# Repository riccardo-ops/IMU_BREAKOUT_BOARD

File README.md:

In this repo, a simple breakout board is made to include an IMU and a barometer.

IMU = LSM6DSV16XTR -> https://www.mouser.it/it/ProductDetail/STMicroelectronics/LSM6DSV16XTR?qs=MyNHzdoqoQLCWe%2FE3pkKcA%3D%3D
Barometer = MS5611-01BA03 -> https://www.te.com/commerce/DocumentDelivery/DDEController?Action=showdoc&DocId=Data+Sheet%7FMS5611-01BA03%7FB3%7Fpdf%7FEnglish%7FENG_DS_MS5611-01BA03_B3.pdf%7FCAT-BLPS0036

The idea is simple : create a breakout board with two common and low cost sensors that can easily be interfaced with FPGAs, Arduino, STM32, etc.

Some tips for this board : 
- Connectors : simple pin header, every Arduino starter pack has compatible cables.
- User LED : two user controlled LED are put inside this board
- Power on LED : there's an LED connected to the power section of every IC. 
  If something goes wrong with power connections, the LED is a simple, but yet effective way to debug
- TVS Diode : those connectors can easily have transient current peaks. Burn the ICs in not something I want, so this kind of protection is needed.
  Every TVS diode eats some voltage, so keep this in mind when you design your protection module!
- 4 Layer : this can be overkill, but to have a solid ground plane is always a good idea when you use sensible sensors like IMU and barometers.
  In this project the maximum frequency of communication is 5 MHz, so there is no danger for high frequency.

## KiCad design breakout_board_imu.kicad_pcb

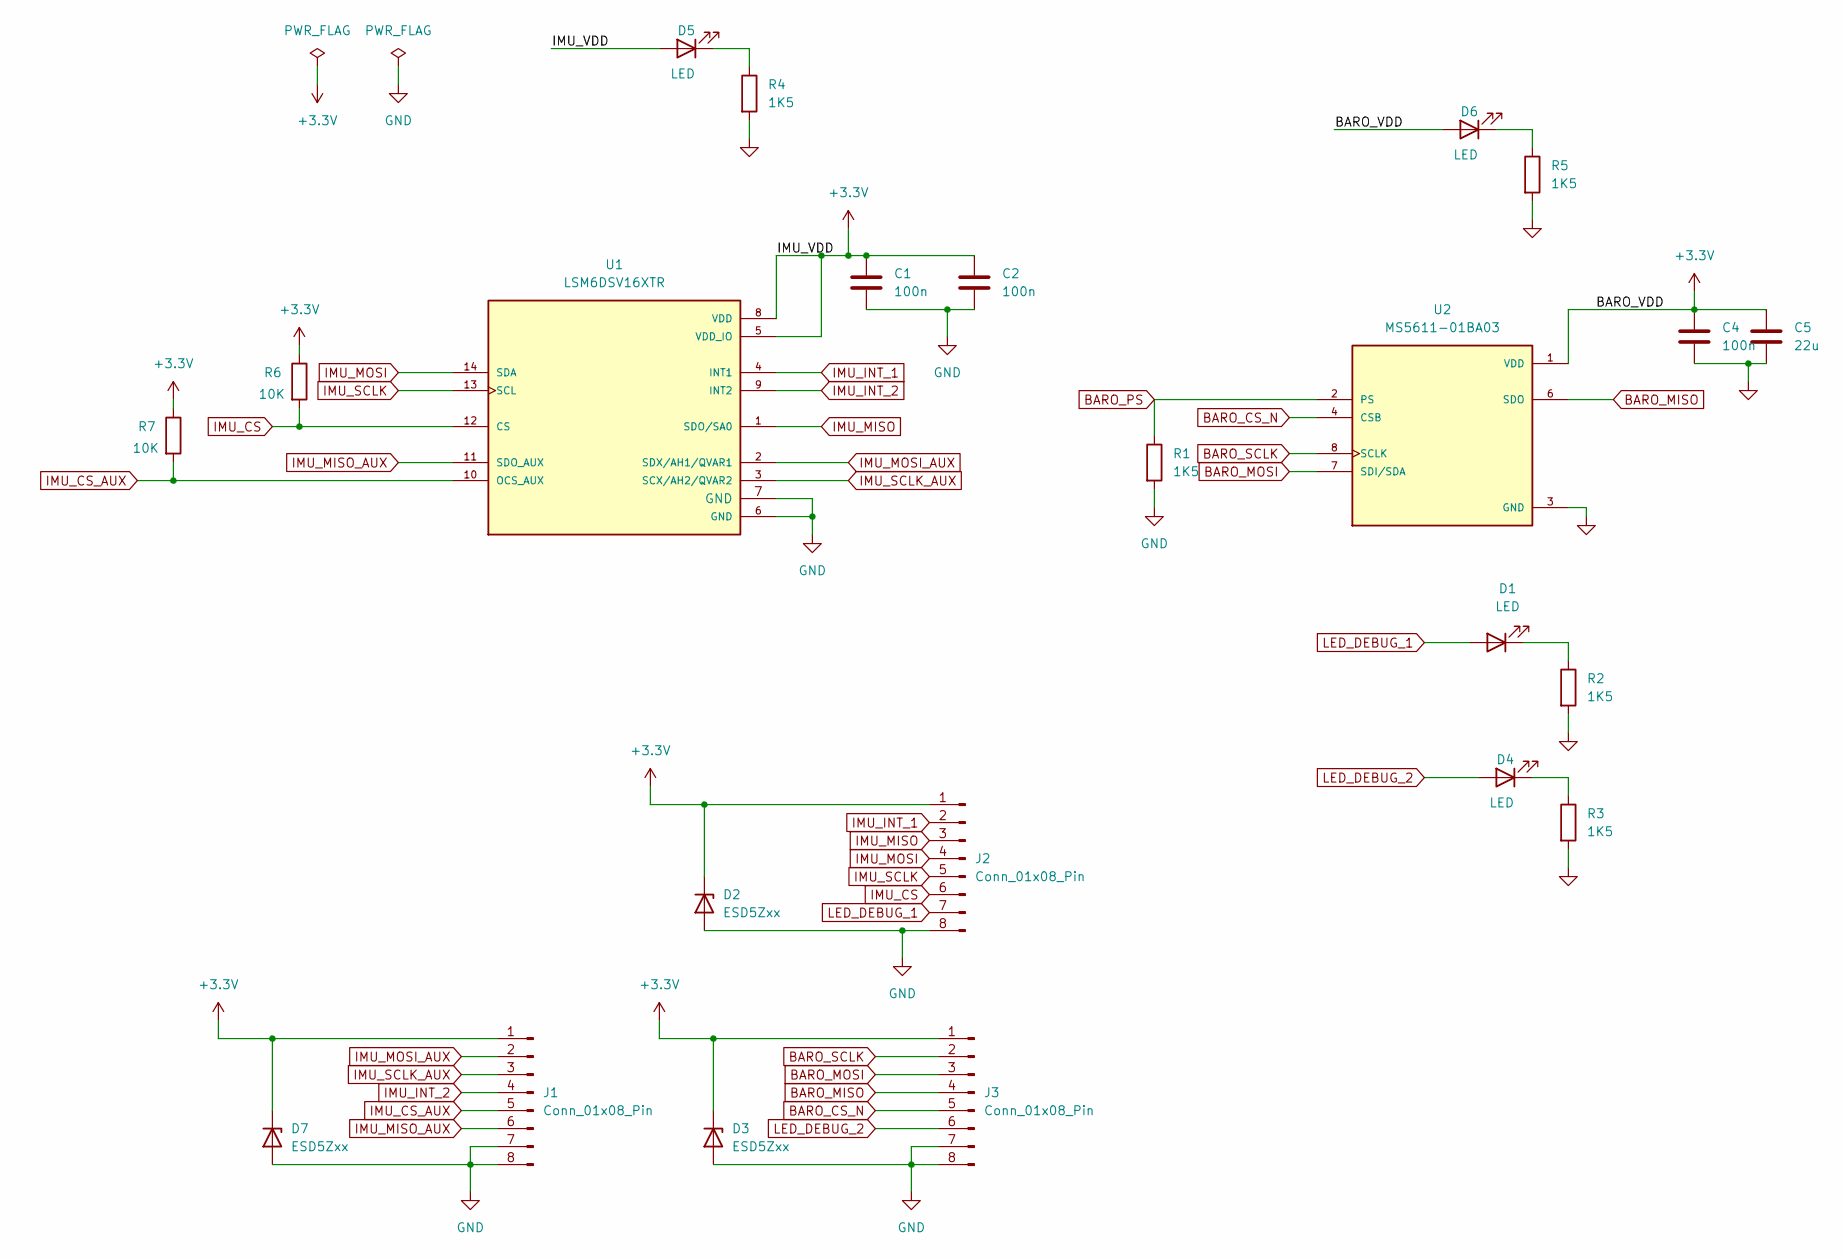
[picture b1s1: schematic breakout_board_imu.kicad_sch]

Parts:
C1, C2, C4: 100n; C_0402_1005Metric
C5: 22u; C_0805_2012Metric
D1, D4, D5, D6: LED; LED_0603_1608Metric
D2, D3, D7: ESD5Zxx; D_SOD-523
J1, J2, J3: Conn_01x08_Pin; PinHeader_1x08_P2.54mm_Vertical
R1, R2, R3, R4, R5: 1K5; R_0402_1005Metric
R6, R7: 10K; R_0805_2012Metric
U1: LSM6DSV16XTR; XDCR_LSM6DSV16XTR; PARTREV 4
U2: MS5611-01BA03; SON125P500X300X100-8N; PARTREV 06/2017

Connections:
+3.3V: C1.1, C2.1, C4.1, C5.1, D2.1 (K), D3.1 (K), D5.2 (A), D6.2 (A), D7.1 (K), J1.1, J2.1, J3.1, R6.1, R7.1, U1.5 (VDD_IO), U1.8 (VDD), U2.1 (VDD)
BARO_CS_N: J3.5, U2.4 (CSB), U2.5 (CSB)
BARO_MISO: J3.4, U2.6 (SDO)
BARO_MOSI: J3.3, U2.7 (SDI/SDA)
BARO_PS: R1.1, U2.2 (PS)
BARO_SCLK: J3.2, U2.8 (SCLK)
GND: C1.2, C2.2, C4.2, C5.2, D2.2 (A), D3.2 (A), D7.2 (A), J1.7, J1.8, J2.8, J3.7, J3.8, R1.2, R2.2, R3.2, R4.2, R5.2, U1.6 (GND), U1.7 (GND), U2.3 (GND)
IMU_CS: J2.6, R6.2, U1.12 (CS)
IMU_CS_AUX: J1.5, R7.2, U1.10 (OCS_AUX)
IMU_INT_1: J2.2, U1.4 (INT1)
IMU_INT_2: J1.4, U1.9 (INT2)
IMU_MISO: J2.3, U1.1 (SDO/SA0)
IMU_MISO_AUX: J1.6, U1.11 (SDO_AUX)
IMU_MOSI: J2.4, U1.14 (SDA)
IMU_MOSI_AUX: J1.2, U1.2 (SDX/AH1/QVAR1)
IMU_SCLK: J2.5, U1.13 (SCL)
IMU_SCLK_AUX: J1.3, U1.3 (SCX/AH2/QVAR2)
LED_DEBUG_1: D1.2 (A), J2.7
LED_DEBUG_2: D4.2 (A), J3.6
unnamed: D1.1 (K), R2.1
unnamed: D4.1 (K), R3.1
unnamed: D5.1 (K), R4.1
unnamed: D6.1 (K), R5.1

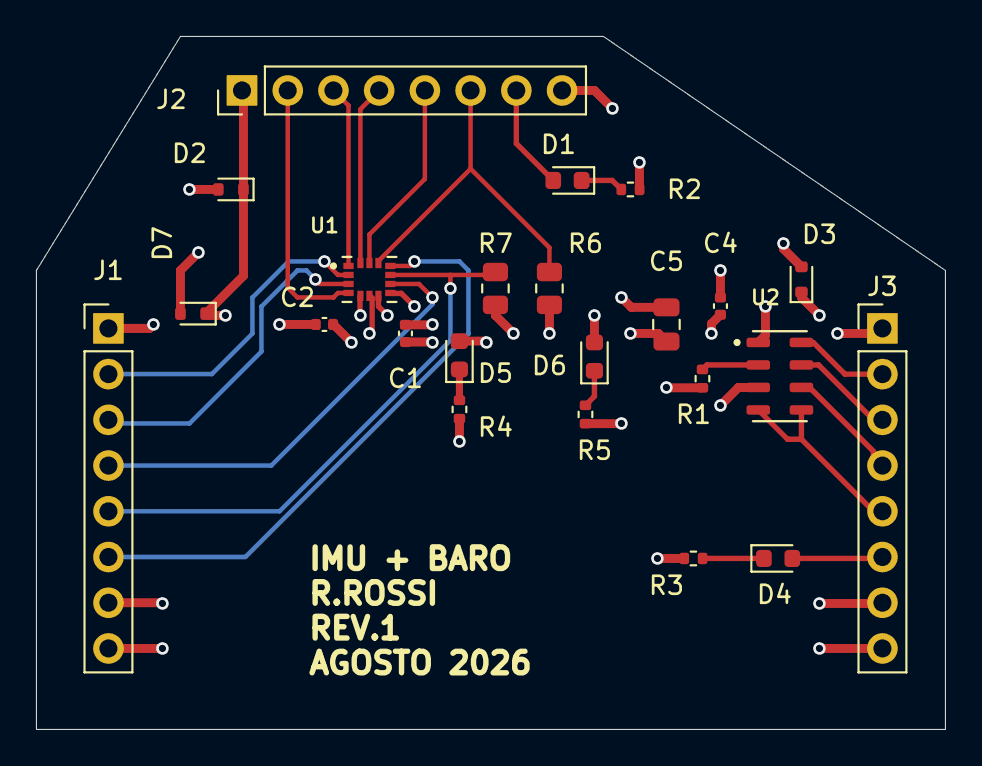
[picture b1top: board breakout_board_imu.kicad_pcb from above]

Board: 4 copper layers, 50.5 x 38.5 mm, 23 parts (0 on the bottom side), 23 nets.

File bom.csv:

"Reference","Value","Datasheet","Footprint","Qty","DNP"
"C1,C3,C4","100n","~","Capacitor_SMD:C_0402_1005Metric","3",""
"C2,C5","22u","~","Capacitor_SMD:C_0805_2012Metric","2",""
"D1,D4,D5,D6","LED","~","LED_SMD:LED_0603_1608Metric","4",""
"D2,D3","ESD5Zxx","https://www.onsemi.com/pdf/datasheet/esd5z2.5t1-d.pdf","Diode_SMD:D_SOD-523","2",""
"J2,J3","Conn_01x08_Pin","~","Connector_PinHeader_2.54mm:PinHeader_1x08_P2.54mm_Vertical","2",""
"R1,R2,R3,R4,R5","1K5","~","Resistor_SMD:R_0402_1005Metric","5",""
"U1","ICM-42688-P","","IMU_ICM_42688_P:PQFN50P300X250X97-14N","1",""
"U2","MS5611-01BA03","","PRESSURE_SENSOR_M5611:SON125P500X300X100-8N","1",""
